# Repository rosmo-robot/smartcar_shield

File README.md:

# Smartcar shield 2.0

A versatile and easy to use vehicle platform for hobby & Academic projects

## Description
This repository, includes everything necessary to set up a Smartcar 2.0. The 100% open hardware robot down to component level.

The Smartcar, is a vehicular educational platform, which enables the user to develop various robotic applications in an affordable, pedagogic and easy way. It is intended to be accessible for persons with basic programming knowledge and little to no experience of electronics. It additionally supports the needs of more experienced users.

## Smartcar 2.0 (In development)

Licence: CERN-OHL-P

 Features;
 
 * Mounting space for SBC; Beagle AI64, Play, Pi, Jetson Nano, etc 
 * Reference implimentation of Arduino / [Smartcar Library](https://github.com/rosmo-robot/smartcar_shield/blob/master/README.md
 * Reference implimentation of [ROS2/Linorobot2](https://github.com/hippo5329/linorobot2_hardware)
 * Use of 4s LifePO4 or 3s Lipo batteries
 * Dual motor drivers for 4x4 & optional [mecanum drive](https://community.robotshop.com/forum/t/nema-17-mecanum-wheels/55901)
 * [mikroBUS socket](https://www.mikroe.com/mikrobus-shuttle-127mm-2x8-pin-box-header-smd-male)
 * Expanded I2C/ SPI connectors using [Breakout Garden](https://shop.pimoroni.com/collections/breakout-garden), [Qwiic](https://soldered.com/categories/easyc-2/)

### Project Status

 * [Motor board](https://kicanvas.org/?github=https://github.com/rosmo-robot/smartcar_shield/blob/master/extras/kicad/V2/Power/Power.kicad_pcb) ordered awaiting testing
   
 * [Pico board](https://kicanvas.org/?github=https://github.com/rosmo-robot/smartcar_shield/blob/master/extras/kicad/V2/Control/Pico/smartcar_control_2.0.kicad_pcb) ordered awaiting testing

We hope Smartcar 2.0 interesting to makers, schools and universities. We realise there's no such thing as a universal robot platform, and there are risks in trying to be all things to all people. We however drawn to seeing what's possible with modularity and testing the edges of interoperability.

### Smartcar 2.0 BOM (In development)

* 1 x [Motor board](https://kicanvas.org/?github=https://github.com/rosmo-robot/smartcar_shield/blob/master/extras/kicad/V2/Power/Power.kicad_pcb) ordered awaiting testing £11
* 1 X [Pico board](https://kicanvas.org/?github=https://github.com/rosmo-robot/smartcar_shield/blob/master/extras/kicad/V2/Control/Pico/smartcar_control_2.0.kicad_pcb) £5
* 4 x [Brushed motors](https://www.aliexpress.com/item/1005004242997257.html) (530rpm @ 12V) £40.50
* 1 x [Olimex Pico](https://www.olimex.com/Products/MicroPython/RP2040-PICO30/open-source-hardware)
* 2 x [40pin 2.54 pitch long male pin headers]()
* 1 x 3S [LifePO4 -recommended](https://www.pulsebattery.com/pages/search-results-page?q=lifePO4%203s) 105 x 33 x 25 or potentially dangerous 3S Lipo battery 135mm*42mm*25mm 304g [~$21 2200Mah](https://www.aliexpress.com/item/1005001419560964.html) > [~$38 4000Mah](https://www.aliexpress.com/item/1005004335619259.html) 135x42x21
* 2 x [Front Bumper](https://www.aliexpress.com/item/1005005024927428.html)

### Optional add ons

* - x [VL45L0x ToF distance sensors](https://shop.pimoroni.com/collections/breakout-garden?tags=Robotics) (optional)
* - X [BNO-85 IMU](https://learn.adafruit.com/adafruit-9-dof-orientation-imu-fusion-breakout-bno085?view=all) (Optional)
* - X [Servo controller](https://www.tindie.com/products/alexchu/zio-16-servo-controller-qwiic/)
* - X [line follower board](https://www.smart-prototyping.com/Zio-Line-Finder-Qwiic-4-Transceivers)
* - X [SPI or I2C Click boards](https://www.mikroe.com/click?interface*=spi,i2c,spi,i2c)
* - X [Aluminum base plate](https://www.aliexpress.com/i/4000265488897.html)
* - Whatever you can bolt to your compute module and get ROS2 to understand, eg cameras, Lidar

### Optional alternative Microcontroller Esp32 S3 (Waveshare)
- Used with [Smartcar Library](https://github.com/platisd/smartcar_shield#software)
- [Linorobot 2 via wifi transport](https://github.com/hippo5329/linorobot2_hardware)
- May also support [Microblocks](https://microblocks.fun/) 

### Single Board Computers (SBC)

We intend to develop some scripts for setting up robotics software on commonly used Single Board Computers which can be added to the basic microcontroller based platform. The OS will be Ubuntu 22.04 LTS. 

The supported hardware may include; 
- [Yuzuki chameleon (OSHW)](https://github.com/YuzukiHD/YuzukiChameleon)
- [Beaglebone Play](https://www.beagleboard.org/boards/beagleplay)
- [Beaglebone Ai-64 (OSHW)](https://beagleboard.org/ai-64) 

Installed software may include

 - Block editor code (TBC)
 - [Pyrobots](https://www.csc.liv.ac.uk/~lad/pyrobots/exercises.html) configuration script
 - [Python app providing a Webui for teleop](https://github.com/DIT112-V19/group-03) Pi GPIO > Micromod.  
 - [Python Robotics](https://github.com/AtsushiSakai/PythonRobotics) Pi GPIO > Micromod
 - [ROS2/Linorobot2](https://github.com/linorobot/linorobot2#linorobot2) USB > Micromod
 - [Rosboard](https://github.com/dheera/rosboard#rosboard) USB > Micromod
 - [Visual circuit](https://github.com/JdeRobot/VisualCircuit#visual-circuit) USB > Micromod
  - [LGPIO](https://ubuntu.com/tutorials/gpio-on-raspberry-pi#1-overview) & [script to set up GPIO](http://4tronix.co.uk/pi2go2/ipd03.py)
 - [Wetty](https://github.com/butlerx/wetty) with [Kaa](http://kaaedit.github.io/)
 - Some demo computer vision code

Linorobot:

### BLDC Version
- Offering an alternate/upgraded BLDC motor board using SimpleFOC, but re-using the 'Modules' board
- Perhaps using [Nema17 BLDC](https://www.omc-stepperonline.com/brushless-dc-motor?mfp=184-frame-size-mm[Nema%2017%20(42%20x%2042)]) to give access to [brackets](https://www.omc-stepperonline.com/nema-17-bracket-for-stepper-motor-and-geared-stepper-motor-alloy-steel-bracket-st-m1) & [gearboxes](https://www.aliexpress.com/premium/nema-17-gearbox.html)

### License
MIT & CERN-OHL-P for Smartcar 2.0 hardware

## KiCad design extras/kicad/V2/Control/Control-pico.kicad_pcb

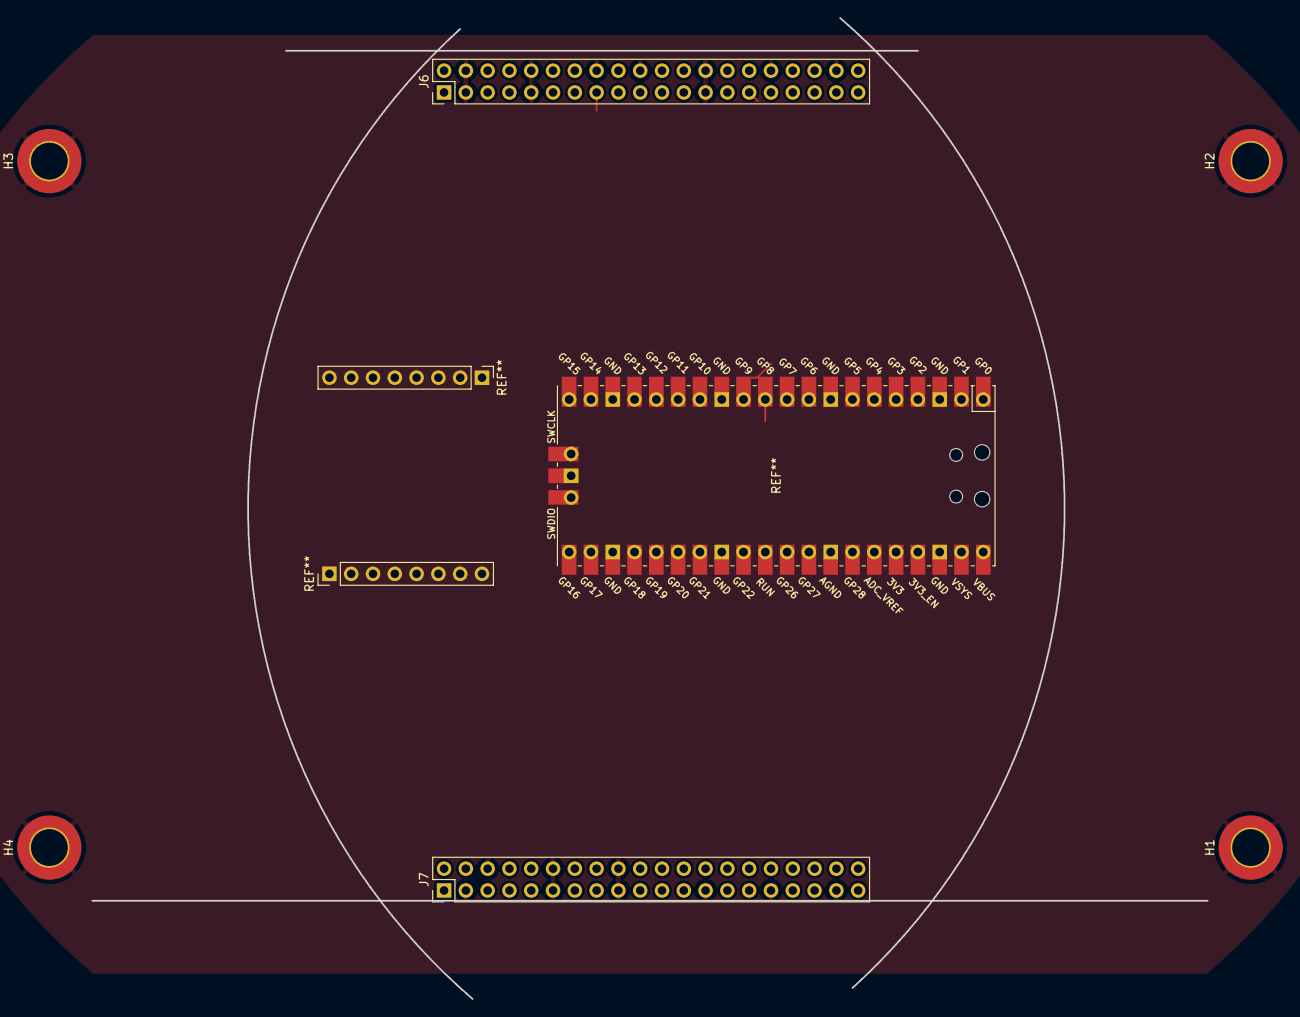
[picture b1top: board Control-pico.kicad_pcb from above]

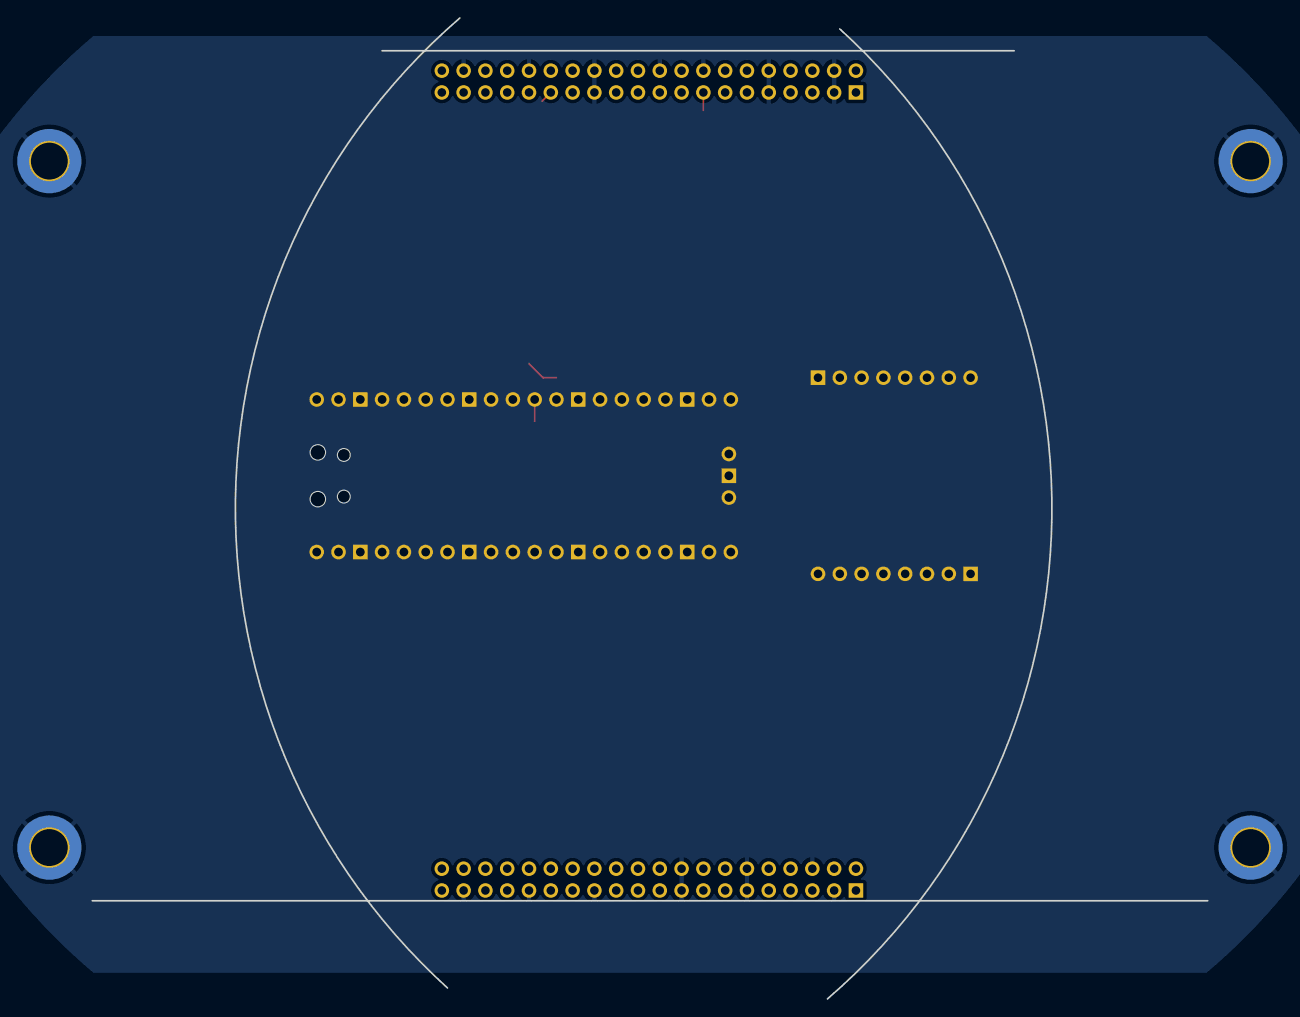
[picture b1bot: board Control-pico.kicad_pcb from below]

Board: 2 copper layers, 130.0 x 114.3 mm, 8 parts (2 on the bottom side), 3 nets.

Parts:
H1, H2, H3, H4: Hole; MountingHole_4.3mm_M4_DIN965_Pad_TopBottom
J6: left; PinHeader_2x20_P2.54mm_Vertical
J7: right; PinHeader_2x20_P2.54mm_Vertical
MH1, MH2: MountingHole_3.2mm_M3_DIN965

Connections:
+3V3: J6.5, J6.6, J6.7, J6.8, J6.19, J6.31, J7.30, J7.38
+5V: J7.13, J7.14, J7.15, J7.16
GND: H1.1, H2.1, H3.1, H4.1, J6.3, J6.4, J6.9, J6.10, J6.16, J6.20, J6.21, J6.25, J6.26, J6.32, J6.33, J6.38, J7.3, J7.6, J7.11, J7.12, J7.17, J7.18, J7.25, J7.31, J7.32, J7.37, J7.40

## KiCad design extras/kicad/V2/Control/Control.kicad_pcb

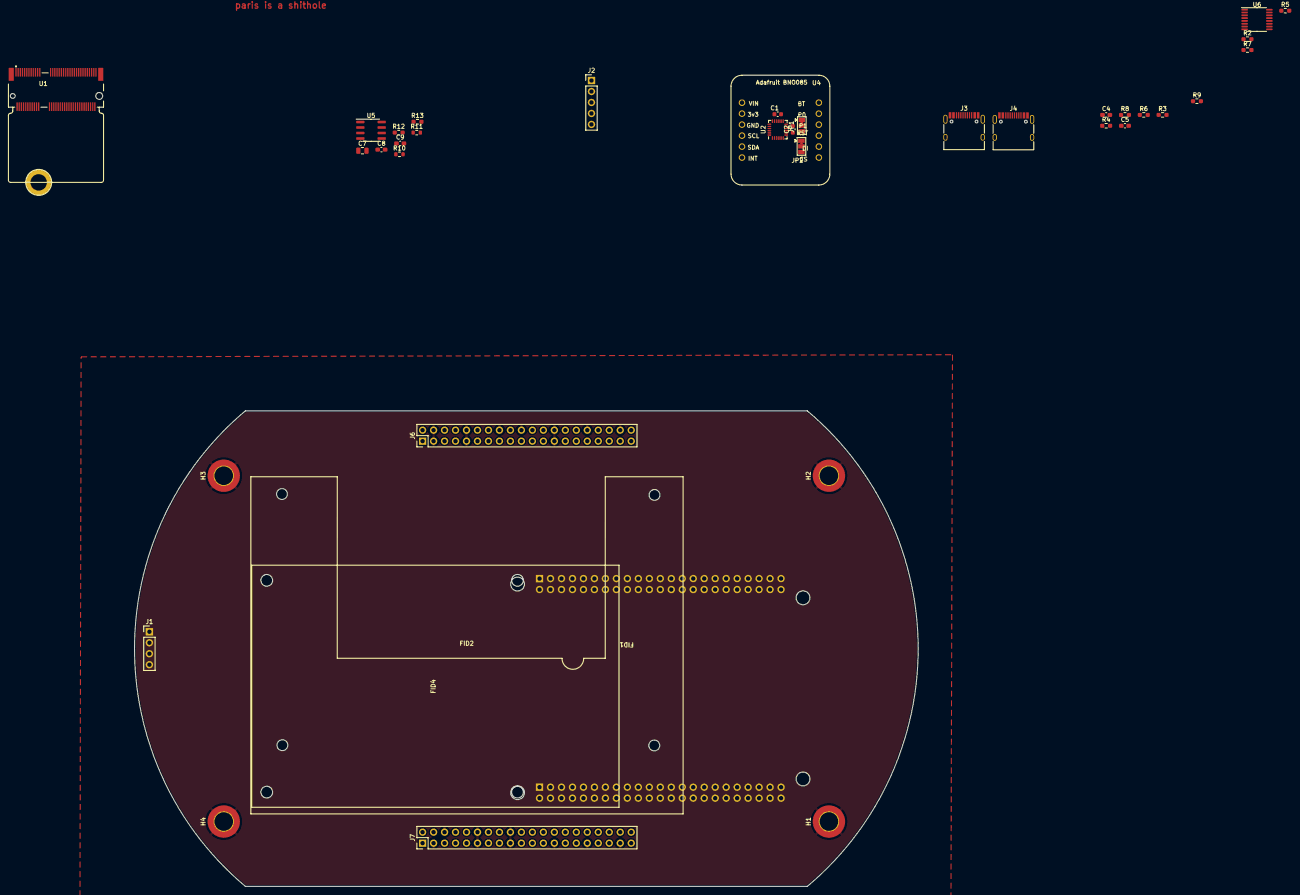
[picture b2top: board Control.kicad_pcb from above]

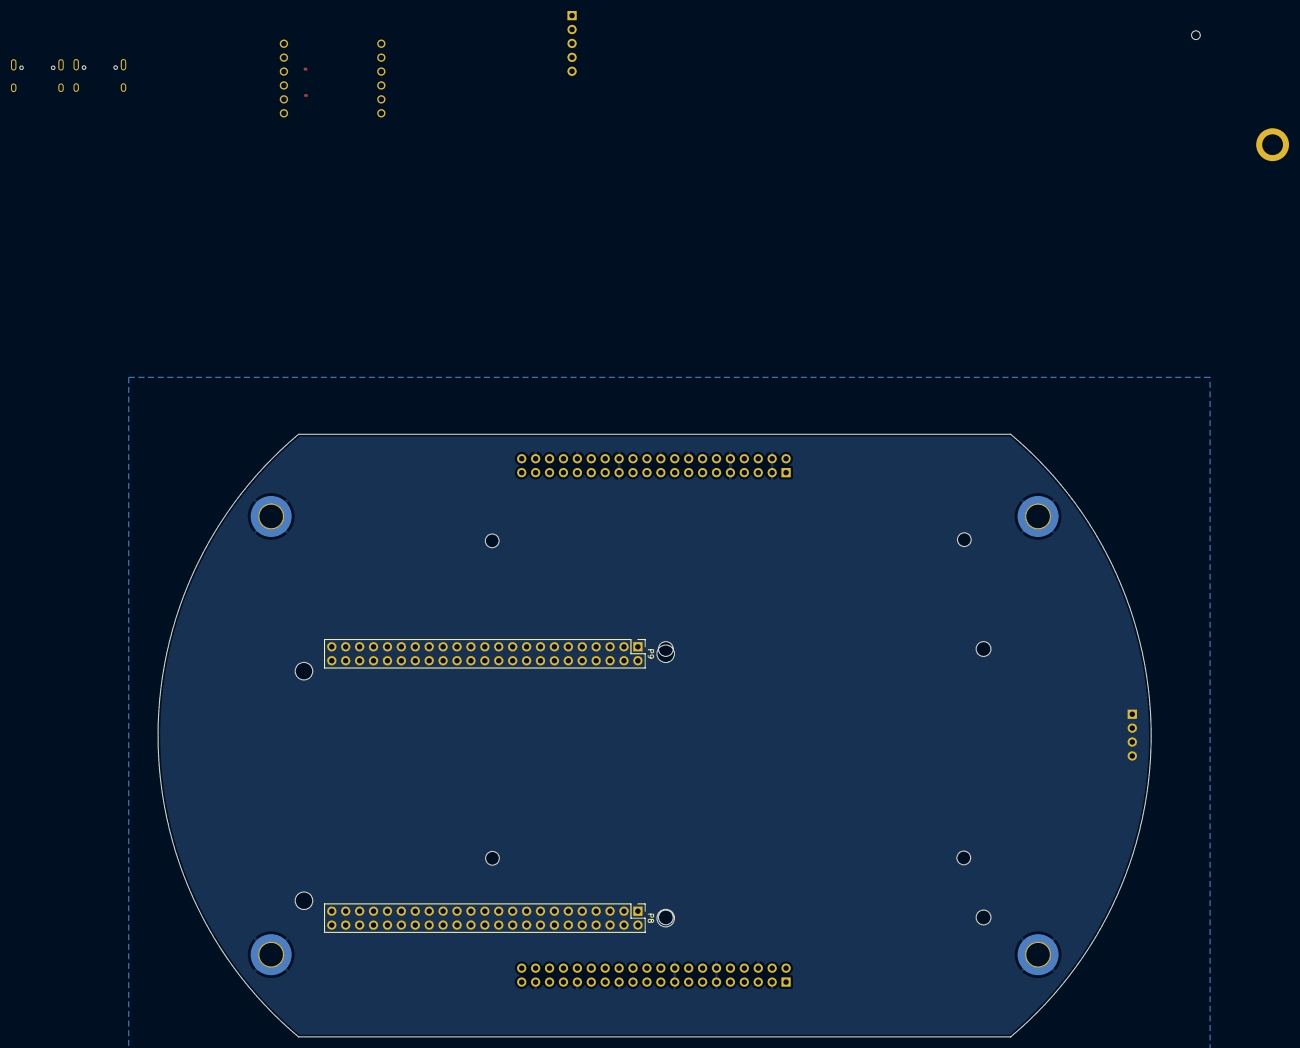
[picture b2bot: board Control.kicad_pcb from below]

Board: 2 copper layers, 181.3 x 110.0 mm, 45 parts (6 on the bottom side), 45 nets, no tracks yet.

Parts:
C1, C2: 100n; C_0603_1608Metric
C4, C8, C9: 100n; C_0603_1608Metric_Pad1.08x0.95mm_HandSolder
C5: 15p; C_0603_1608Metric_Pad1.08x0.95mm_HandSolder
C7: 22u; C_0805_2012Metric
FID1: Fiducial; AI-64
FID2: Fiducial; Jetson-NANO-mechanical
FID4: Fiducial; RPI4B-mechanical
H1, H2, H3, H4: Hole; MountingHole_4.3mm_M4_DIN965_Pad_TopBottom
J1: Ultrasonic Ranging; PinHeader_1x04_P2.54mm_Vertical
J2: Conn_01x05; PinHeader_1x05_P2.54mm_Vertical
J3: Output; USB_C_Receptacle_HRO_TYPE-C-31-M-12
J4: Input; USB_C_Receptacle_HRO_TYPE-C-31-M-12
J6: left; PinHeader_2x20_P2.54mm_Vertical
J7: right; PinHeader_2x20_P2.54mm_Vertical
JP1, JP2: set; SolderJumper-3_P1.3mm_Bridged12_Pad1.0x1.5mm
MH1, MH2, MH3, MH4: MountingHole_3.2mm_M3_DIN965
P8, P9: BeagleBone_Black_Header; PinHeader_2x23_P2.54mm_Vertical
R2: 2k7; R_0603_1608Metric_Pad0.98x0.95mm_HandSolder
R3, R4, R5, R6: 5k1; R_0603_1608Metric_Pad0.98x0.95mm_HandSolder
R7, R8: 1k; R_0603_1608Metric_Pad0.98x0.95mm_HandSolder
R9: 1Meg; R_0603_1608Metric_Pad0.98x0.95mm_HandSolder
R10, R11: 10k; R_0603_1608Metric
R12, R13: 120; R_0603_1608Metric_Pad0.98x0.95mm_HandSolder
U1: SparkFun-micromod; SparkFun-micromod-footprint
U2: MPU-6050; InvenSense_QFN-24_4x4mm_P0.5mm
U4: BNO085-breackout
U5: TJA1042T-3; SOIC-8_3.9x4.9mm_P1.27mm
U6: PCA9557PW; TSSOP-16_4.4x5mm_P0.65mm

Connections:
+3V3: C1.1, C2.1, C4.1, C9.1, J1.4, J2.5, J6.5, J6.6, J6.7, J6.8, J6.19, J6.31, J7.30, J7.38, JP1.3 (B), JP2.3 (B), P9.3, P9.4, R2.1, R7.1, R8.2, R10.1, R11.1, U1.2 (3v3), U1.74 (3V3), U2.8 (VDDIO), U2.13 (VDD), U4.1 (VIN), U5.5 (VIO), U6.16 (VDD)
+5V: C7.1, C8.1, J7.13, J7.14, J7.15, J7.16, P9.5, P9.6, U5.3 (VCC)
/CAN_H: R12.1, R13.1, U5.7 (CANH)
/CAN_L: R12.2, R13.2, U5.6 (CANL)
/Green_1: J6.29, U1.56 (AUD_OUT)
/Green_2: J6.17, U1.51 (I2C_SDA1)
/Green_3: J7.36, U1.52 (AUD_LRCLK)
/Green_4: J7.28, U1.17 (UART_TX1)
/INT_1: J2.2, U1.16 (I2C_INT), U2.12 (INT), U4.6 (INT)
/cc1: J3.A5 (CC1), J4.A5 (CC1), R3.1, R4.1
/cc2: J3.B5 (CC2), J4.B5 (CC2), R5.1, R6.1
/yellow_1: J6.27, U1.54 (AUD_IN)
/yellow_2: J6.15, U1.53 (I2C_SCL1)
/yellow_3: J7.34, U1.50 (AUD_BCLK)
/yellow_4: J7.26, U1.19 (UART_RX1)
AIN1_1: J6.39, U1.40 (G0/BUS0)
AIN1_2: J7.8, U1.48 (G4/BUS4)
AIN2_1: J6.37, U1.42 (G1/BUS1)
AIN2_2: J7.9, U1.44 (G2/BUS2)
BIN1_1: J6.34, U1.34 (A0)
BIN1_2: J7.5, U1.46 (G3/BUS3)
BIN2_1: J6.36, U1.38 (A1)
BIN2_2: J7.4, U1.73 (G5/BUS5)
D2+: J4.A6 (D+), J4.B6 (D+), U1.3 (USB_D+)
D2-: J4.A7 (D-), J4.B7 (D-), U1.5 (USB_D-)
D+: J3.A6 (D+), J3.B6 (D+)
D-: J3.A7 (D-), J3.B7 (D-)
GND: C1.2, C2.2, C4.2, C5.2, C7.2, C8.2, C9.2, H1.1, H2.1, H3.1, H4.1, J1.1, J2.1, J3.A1 (GND), J3.A12 (GND), J3.B1 (GND), J3.B12 (GND), J4.A1 (GND), J4.A12 (GND), J4.B1 (GND), J4.B12 (GND), J6.3, J6.4, J6.9, J6.10, J6.16, J6.20, J6.21, J6.25, J6.26, J6.32, J6.33, J6.38, J7.3, J7.6, J7.11, J7.12, J7.17, J7.18, J7.25, J7.31, J7.32, J7.37, J7.40, JP1.1 (A), JP2.1 (A), P8.1, P8.2, P8.45, P9.1, P9.2, P9.34, P9.43, P9.44, P9.45, P9.46, R3.2, R4.2, R5.2, R6.2, R9.1, U1.1 (GND), U1.7 (GND), U1.33 (GND), U1.36 (GND), U1.39 (GND), U1.45 (GND), U1.75 (GND), U2.18 (GND), U4.3 (GND), U5.2 (GND), U6.5 (A2), U6.8 (VSS)
unnamed: C5.1, J3.S1 (SHIELD), R9.2
unnamed: JP1.2 (C), U2.9 (AD0)
unnamed: JP2.2 (C), U4.8 (DI)
unnamed: R2.2, U6.15 (~RESET)
unnamed: R7.2, U6.3 (A0)
unnamed: R8.1, U6.4 (A1)
PWMA_1: J6.35, U1.10 (D0)
PWMA_2: J7.10, U1.18 (D1)
PWMB_1: J6.40, U1.32 (PWM0)
PWMB_2: J7.2, U1.47 (PWM1)
SCL: J1.3, J2.3, J6.1, P9.19, R10.2, U1.14 (I2C_SCL), U2.23 (SCL), U4.4 (SCL), U6.1 (SCL)
SDA: J1.2, J2.4, J6.2, P9.20, R11.2, U1.12 (I2C_SDA), U2.24 (SDA), U4.5 (SDA), U6.2 (SDA)
SPI_CS: P9.17, U1.55 (SPI_CS)
SPI_MISO: P9.29, U1.59 (SPI_COPI_(MOSI))
SPI_MOSI: P9.30, U1.61 (SPI_CIPO_(MISO))
SPI_SCK: P9.31, U1.57 (SPI_SCK)
VBUS: J3.A4 (VBUS), J3.A9 (VBUS), J3.B4 (VBUS), J3.B9 (VBUS), J4.A4 (VBUS), J4.A9 (VBUS), J4.B4 (VBUS), J4.B9 (VBUS), P9.7, P9.8

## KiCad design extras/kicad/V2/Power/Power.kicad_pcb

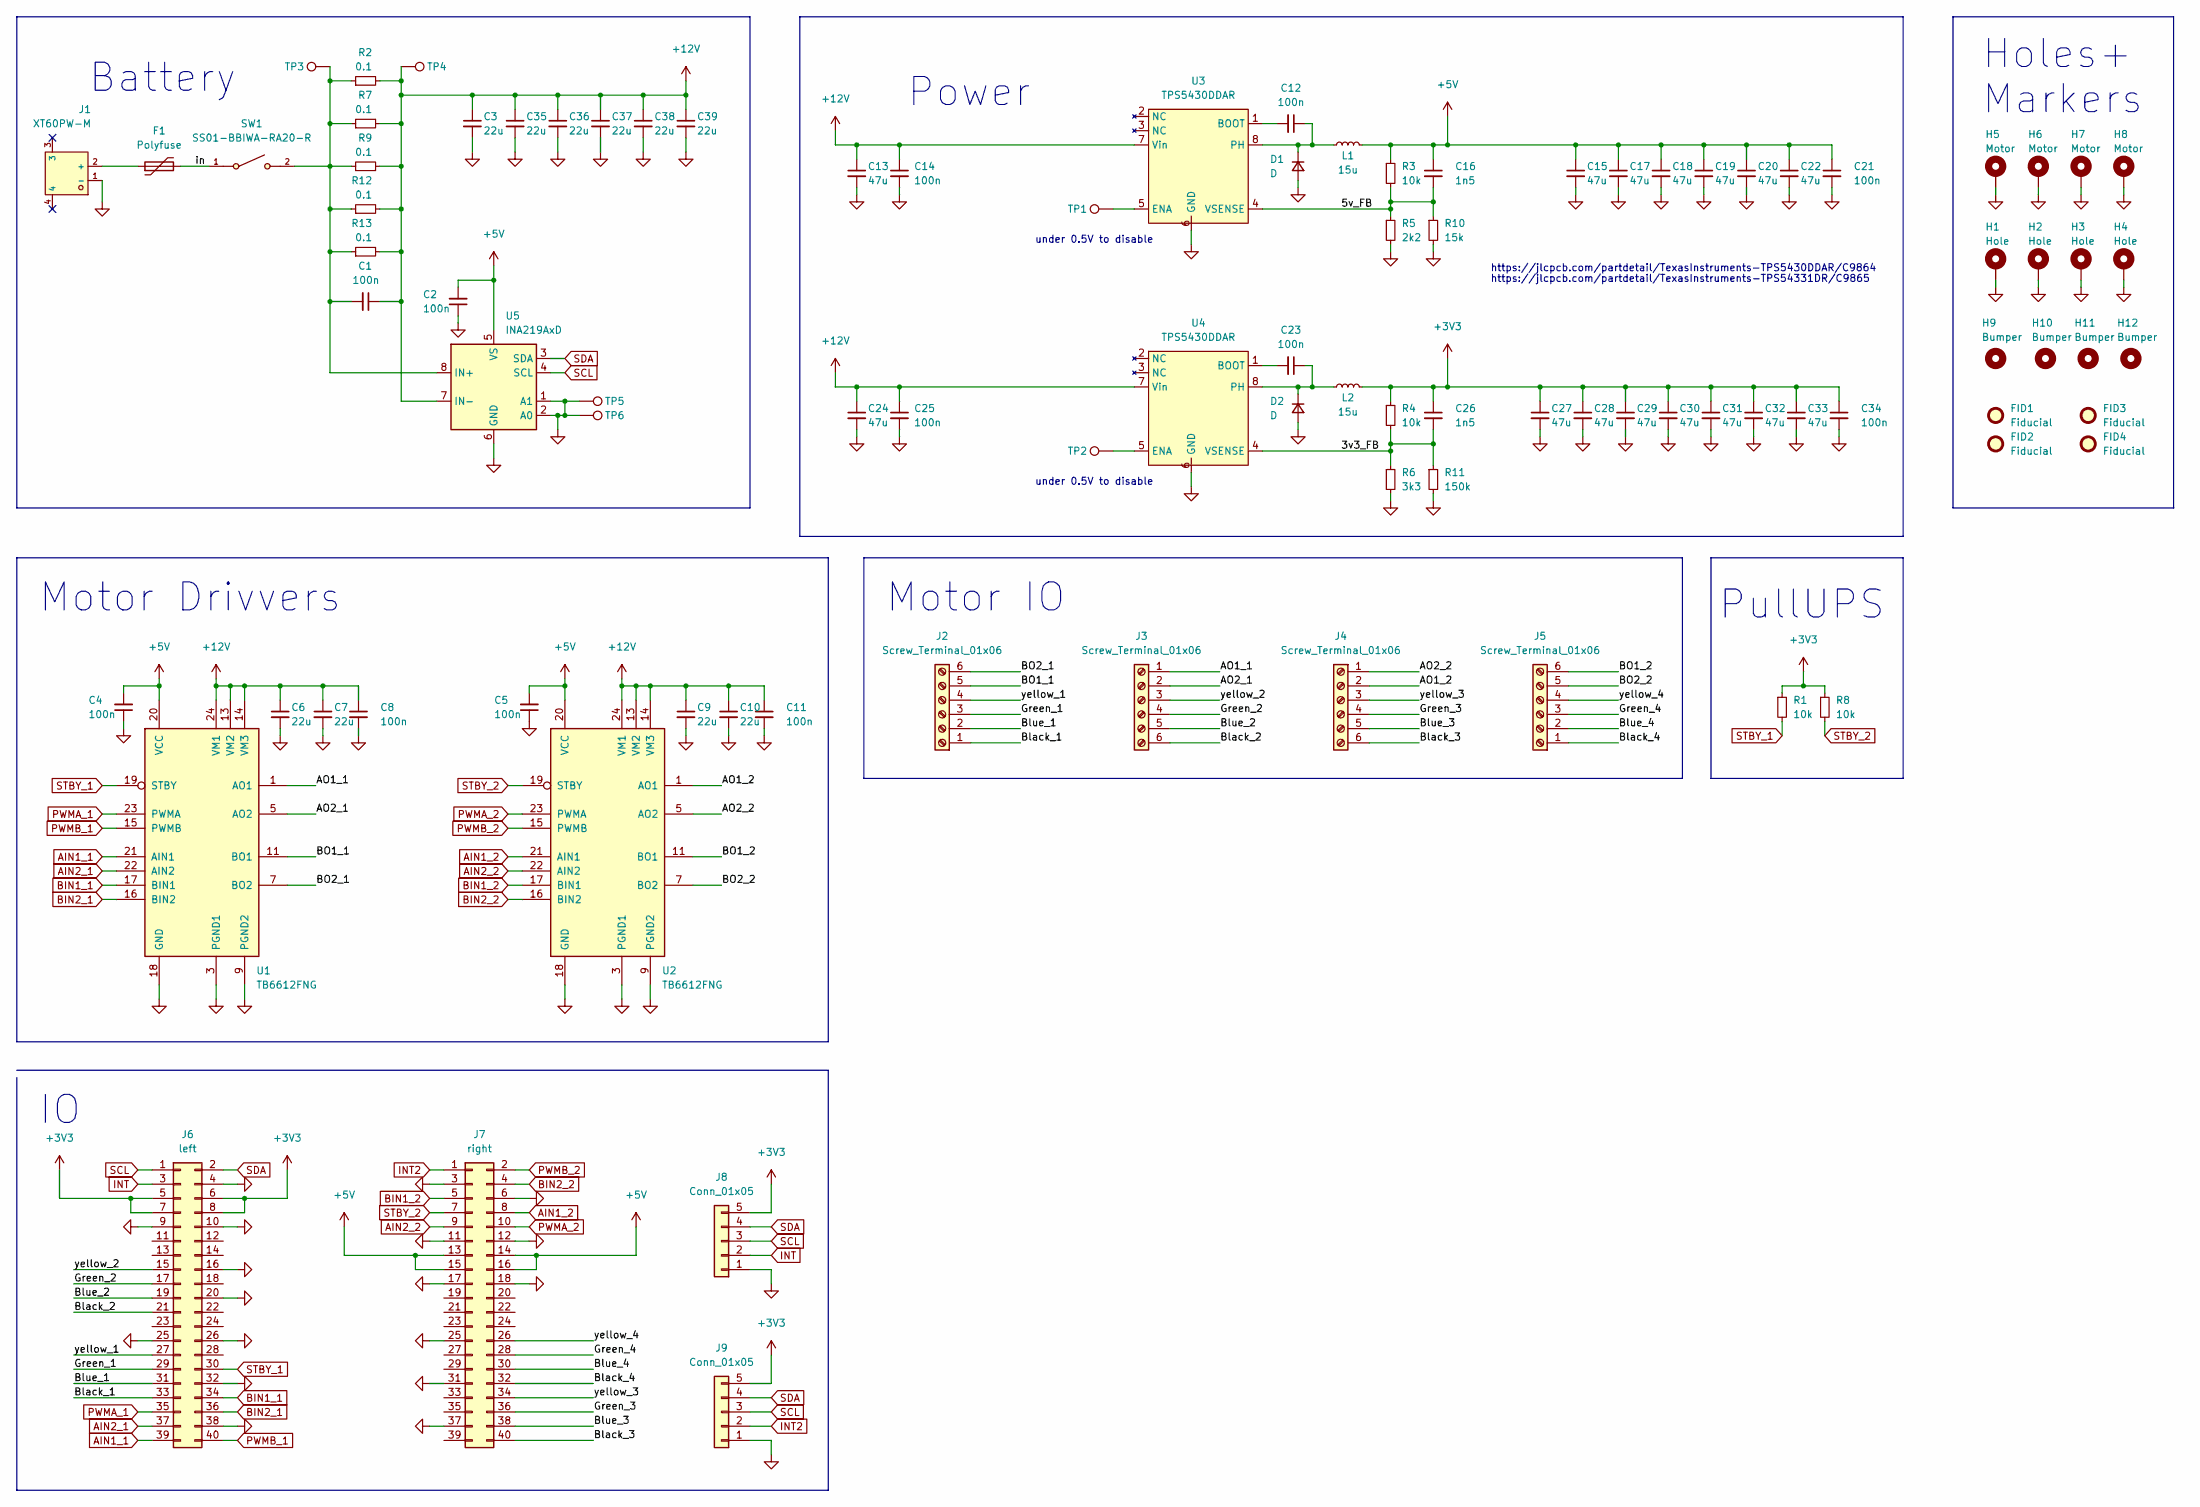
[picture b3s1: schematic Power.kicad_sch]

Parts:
C1, C2, C4, C5, C8, C11, C12, C14, C21, C23, C25, C34: 100n; C_0603_1608Metric; LCSC C14663
C3, C6, C7, C9, C10, C35, C36, C37, C38, C39: 22u; C_0805_2012Metric; LCSC C45783
C13, C15, C17, C18, C19, C20, C22, C24, C27, C28, C29, C30, C31, C32, C33: 47u; C_1206_3216Metric; LCSC C96123
C16, C26: 1n5; C_0603_1608Metric_Pad1.08x0.95mm_HandSolder; LCSC C1595
D1, D2: D; D_SMA; LCSC C22452
F1: Polyfuse; Fuse_2920_7451Metric_Pad2.10x5.45mm_HandSolder
FID1: Fiducial; Fiducial_0.5mm_Mask1mm
FID2: Fiducial; WEEE-Logo_5.6x8mm_SilkScreen
FID3: Fiducial; OSHW-Logo2_14.6x12mm_SilkScreen
FID4: Fiducial; KiCad-Logo2_6mm_SilkScreen
H1, H2, H3, H4: Hole; MountingHole_4.3mm_M4_DIN965_Pad_TopBottom
H5, H6, H7, H8: Motor; JGA25-370 DC motor
H9, H10, H11, H12: Bumper; MountingHole_4.5mm
J1: XT60PW-M; CONN-TH_XT60PW-M; LCSC C98732
J2, J3, J4, J5: Screw_Terminal_01x06; TerminalBlock_4Ucon_1x06_P3.50mm_Horizontal
J6: left; PinHeader_2x20_P2.54mm_Vertical
J7: right; PinHeader_2x20_P2.54mm_Vertical
J8, J9: Conn_01x05; PinHeader_1x05_P2.54mm_Vertical
L1, L2: 15u; Inductor SMD,11.6x10.1x4mm; LCSC C3002687
R1, R3, R4, R8: 10k; R_0603_1608Metric; LCSC C25804
R2, R7, R9, R12, R13: 0.1; R_1206_3216Metric_Pad1.30x1.75mm_HandSolder; LCSC C25334
R5: 2k2; R_0603_1608Metric_Pad0.98x0.95mm_HandSolder; LCSC C4190
R6: 3k3; R_0603_1608Metric_Pad0.98x0.95mm_HandSolder; LCSC C22978
R10: 15k; R_0603_1608Metric_Pad0.98x0.95mm_HandSolder; LCSC C22809
R11: 150k; R_0603_1608Metric_Pad0.98x0.95mm_HandSolder; LCSC C22807
SW1: SS01-BBIWA-RA20-R; SW-TH_SS01-BBIWA-RA20-R; LCSC C309065
TP1, TP2, TP3, TP4, TP5, TP6: TestPoint; TestPoint_Pad_D1.0mm
U1, U2: TB6612FNG; SSOP-24_5.3x8.2mm_P0.65mm; LCSC C88224
U3, U4: TPS5430DDAR; SOIC-8-1EP_3.9x4.9mm_P1.27mm_EP2.29x3mm_ThermalVias; LCSC C9864
U5: INA219AxD; SOIC-8_3.9x4.9mm_P1.27mm; LCSC C138706

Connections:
+3V3: C26.1, C27.1, C28.1, C29.1, C30.1, C31.1, C32.1, C33.1, C34.1, J6.5, J6.6, J6.7, J6.8, J8.5, J9.5, L2.2, R1.1, R4.1, R8.1
+5V: C2.2, C4.2, C5.2, C15.1, C16.1, C17.1, C18.1, C19.1, C20.1, C21.1, C22.1, J7.13, J7.14, J7.15, J7.16, L1.2, R3.1, U1.20 (VCC), U2.20 (VCC), U5.5 (VS)
+12V: C1.1, C3.1, C6.1, C7.1, C8.1, C9.1, C10.1, C11.1, C13.1, C14.1, C24.1, C25.1, C35.1, C36.1, C37.1, C38.1, C39.1, R2.2, R7.2, R9.2, R12.2, R13.2, TP4.1, U1.13 (VM2), U1.14 (VM3), U1.24 (VM1), U2.13 (VM2), U2.14 (VM3), U2.24 (VM1), U3.7 (Vin), U4.7 (Vin), U5.7 (IN-)
/3v3_FB: C26.2, R4.2, R6.1, R11.1, U4.4 (VSENSE)
/5v_FB: C16.2, R3.2, R5.1, R10.1, U3.4 (VSENSE)
/AO1_1: J3.1, U1.1 (AO1), U1.2 (AO1)
/AO1_2: J4.2, U2.1 (AO1), U2.2 (AO1)
/AO2_1: J3.2, U1.5 (AO2), U1.6 (AO2)
/AO2_2: J4.1, U2.5 (AO2), U2.6 (AO2)
/BO1_1: J2.5, U1.11 (BO1), U1.12 (BO1)
/BO1_2: J5.6, U2.11 (BO1), U2.12 (BO1)
/BO2_1: J2.6, U1.7 (BO2), U1.8 (BO2)
/BO2_2: J5.5, U2.7 (BO2), U2.8 (BO2)
/Black_1: J2.1, J6.33
/Black_2: J3.6, J6.21
/Black_3: J4.6, J7.40
/Black_4: J5.1, J7.32
/Blue_1: J2.2, J6.31
/Blue_2: J3.5, J6.19
/Blue_3: J4.5, J7.38
/Blue_4: J5.2, J7.30
/Green_1: J2.3, J6.29
/Green_2: J3.4, J6.17
/Green_3: J4.4, J7.36
/Green_4: J5.3, J7.28
/in: F1.2, SW1.1
/yellow_1: J2.4, J6.27
/yellow_2: J3.3, J6.15
/yellow_3: J4.3, J7.34
/yellow_4: J5.4, J7.26
AIN1_1: J6.39, U1.21 (AIN1)
AIN1_2: J7.8, U2.21 (AIN1)
AIN2_1: J6.37, U1.22 (AIN2)
AIN2_2: J7.9, U2.22 (AIN2)
BIN1_1: J6.34, U1.17 (BIN1)
BIN1_2: J7.5, U2.17 (BIN1)
BIN2_1: J6.36, U1.16 (BIN2)
BIN2_2: J7.4, U2.16 (BIN2)
GND: C2.1, C3.2, C4.1, C5.1, C6.2, C7.2, C8.2, C9.2, C10.2, C11.2, C13.2, C14.2, C15.2, C17.2, C18.2, C19.2, C20.2, C21.2, C22.2, C24.2, C25.2, C27.2, C28.2, C29.2, C30.2, C31.2, C32.2, C33.2, C34.2, C35.2, C36.2, C37.2, C38.2, C39.2, D1.2 (A), D2.2 (A), H1.1, H2.1, H3.1, H4.1, H5.1, H6.1, H7.1, H8.1, J1.1 (-), J6.4, J6.9, J6.10, J6.16, J6.20, J6.25, J6.26, J6.32, J6.38, J7.3, J7.6, J7.11, J7.12, J7.17, J7.18, J7.25, J7.31, J7.37, J8.1, J9.1, R5.2, R6.2, R10.2, R11.2, TP5.1, TP6.1, U1.3 (PGND1), U1.4 (PGND1), U1.9 (PGND2), U1.10 (PGND2), U1.18 (GND), U2.3 (PGND1), U2.4 (PGND1), U2.9 (PGND2), U2.10 (PGND2), U2.18 (GND), U3.6 (GND), U3.9 (Thermal), U4.6 (GND), U4.9 (Thermal), U5.1 (A1), U5.2 (A0), U5.6 (GND)
INT: J6.3, J8.2
INT2: J7.1, J9.2
unnamed: C1.2, R2.1, R7.1, R9.1, R12.1, R13.1, SW1.2, TP3.1, U5.8 (IN+)
unnamed: C12.1, D1.1 (K), L1.1, U3.8 (PH)
unnamed: C12.2, U3.1 (BOOT)
unnamed: C23.1, D2.1 (K), L2.1, U4.8 (PH)
unnamed: C23.2, U4.1 (BOOT)
unnamed: F1.1, J1.2 (+)
unnamed: TP1.1, U3.5 (ENA)
unnamed: TP2.1, U4.5 (ENA)
PWMA_1: J6.35, U1.23 (PWMA)
PWMA_2: J7.10, U2.23 (PWMA)
PWMB_1: J6.40, U1.15 (PWMB)
PWMB_2: J7.2, U2.15 (PWMB)
SCL: J6.1, J8.3, J9.3, U5.4 (SCL)
SDA: J6.2, J8.4, J9.4, U5.3 (SDA)
STBY_1: J6.30, R1.2, U1.19 (STBY)
STBY_2: J7.7, R8.2, U2.19 (STBY)

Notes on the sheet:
Motor IO
https://jlcpcb.com/partdetail/TexasInstruments-TPS5430DDAR/C9864
Motor Drivvers
https://jlcpcb.com/partdetail/TexasInstruments-TPS54331DR/C9865
under 0.5V to disable
PullUPS
Holes+ Markers
Battery
Power

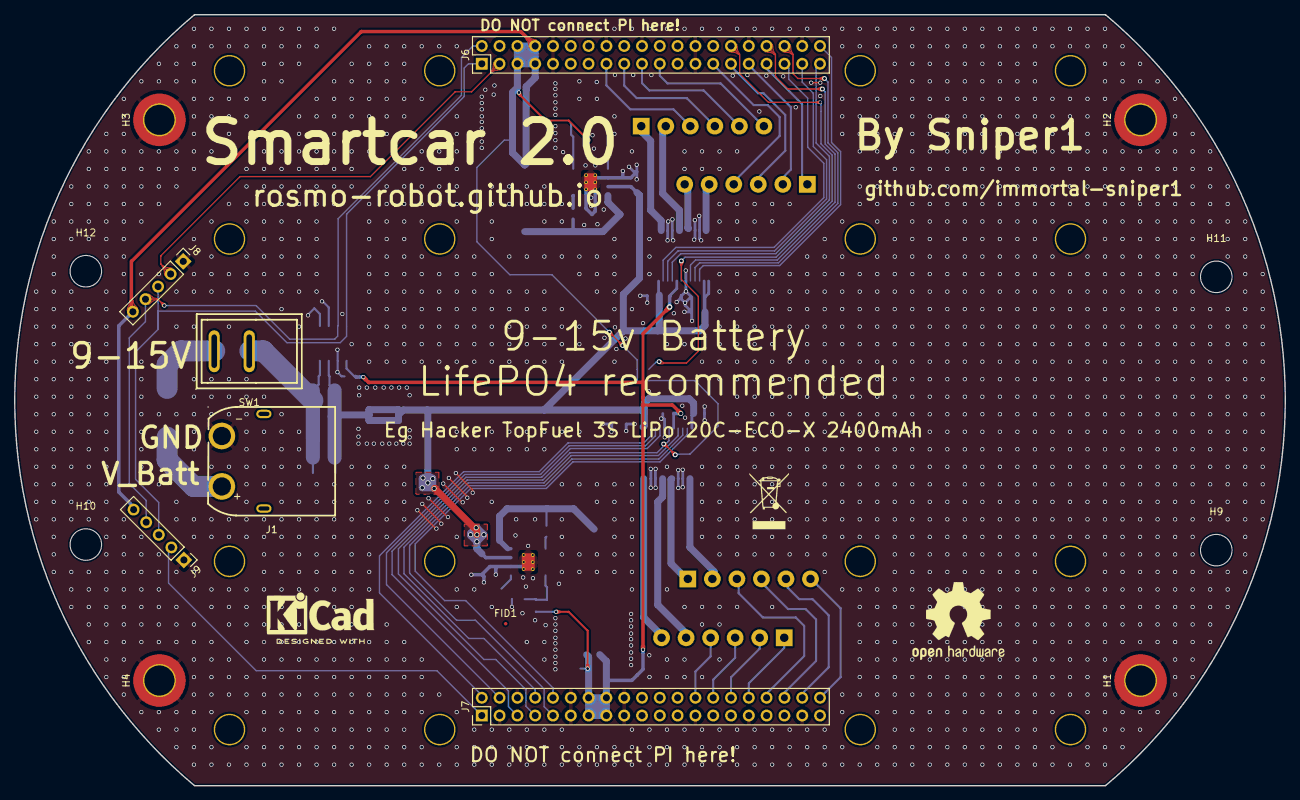
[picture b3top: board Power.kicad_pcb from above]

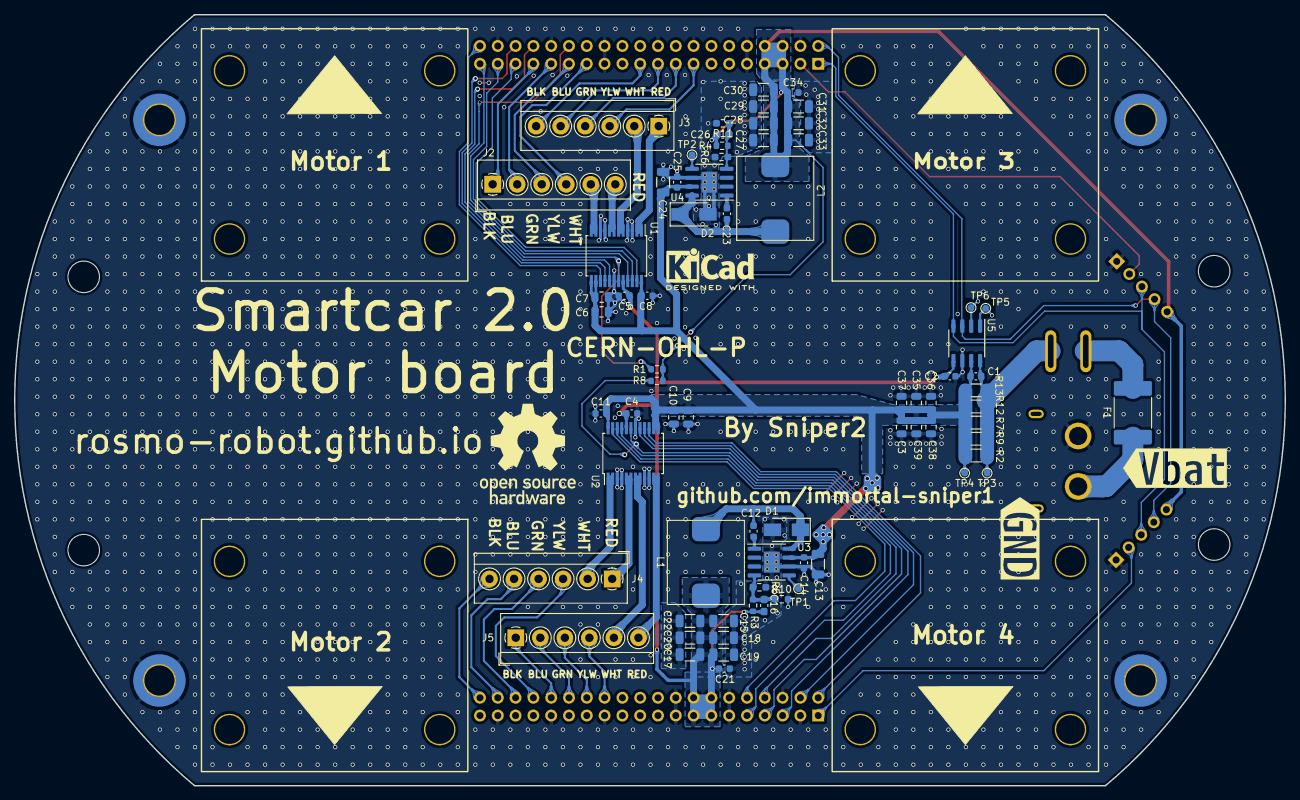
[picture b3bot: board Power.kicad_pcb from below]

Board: 2 copper layers, 181.3 x 110.0 mm, 96 parts (78 on the bottom side), 57 nets.

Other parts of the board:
kibuzzard-63E93541: G***; kibuzzard-63E93541
kibuzzard-63E93553: G***; kibuzzard-63E93553

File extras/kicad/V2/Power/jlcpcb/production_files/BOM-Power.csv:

Comment,Designator,Footprint,LCSC
INA219AxD,U5,SOIC-8_3.9x4.9mm_P1.27mm,C138706
100n,"C1,C11,C12,C14,C2,C21,C23,C25,C34,C4,C5,C8",C_0603_1608Metric,C14663
1n5,"C16,C26",C_0603_1608Metric_Pad1.08x0.95mm_HandSolder,C1595
D,"D1,D2",D_SMA,C22452
150k,R11,R_0603_1608Metric_Pad0.98x0.95mm_HandSolder,C22807
15k,R10,R_0603_1608Metric_Pad0.98x0.95mm_HandSolder,C22809
3k3,R6,R_0603_1608Metric_Pad0.98x0.95mm_HandSolder,C22978
0.1,"R12,R13,R2,R7,R9",R_1206_3216Metric_Pad1.30x1.75mm_HandSolder,C25334
10k,"R1,R3,R4,R8",R_0603_1608Metric,C25804
15u,"L1,L2","Inductor SMD,11.6x10.1x4mm",C3002687
SS01-BBIWA-RA20-R,SW1,SW-TH_SS01-BBIWA-RA20-R,C309065
2k2,R5,R_0603_1608Metric_Pad0.98x0.95mm_HandSolder,C4190
22u,"C10,C3,C35,C36,C37,C38,C39,C6,C7,C9",C_0805_2012Metric,C45783
TB6612FNG,"U1,U2",SSOP-24_5.3x8.2mm_P0.65mm,C88224
47u,"C13,C15,C17,C18,C19,C20,C22,C24,C27,C28,C29,C30,C31,C32,C33",C_1206_3216Metric,C96123
TPS5430DDAR,"U3,U4",SOIC-8-1EP_3.9x4.9mm_P1.27mm_EP2.29x3mm_ThermalVias,C9864
XT60PW-M,J1,CONN-TH_XT60PW-M,C98732
Conn_01x05,J8,PinHeader_1x05_P2.54mm_Vertical,
left,J6,PinHeader_2x20_P2.54mm_Vertical,
Conn_01x05,J9,PinHeader_1x05_P2.54mm_Vertical,
right,J7,PinHeader_2x20_P2.54mm_Vertical,
Polyfuse,F1,Fuse_2920_7451Metric_Pad2.10x5.45mm_HandSolder,
Screw_Terminal_01x06,J3,TerminalBlock_4Ucon_1x06_P3.50mm_Horizontal,
Screw_Terminal_01x06,J5,TerminalBlock_4Ucon_1x06_P3.50mm_Horizontal,
Screw_Terminal_01x06,J4,TerminalBlock_4Ucon_1x06_P3.50mm_Horizontal,
Screw_Terminal_01x06,J2,TerminalBlock_4Ucon_1x06_P3.50mm_Horizontal,

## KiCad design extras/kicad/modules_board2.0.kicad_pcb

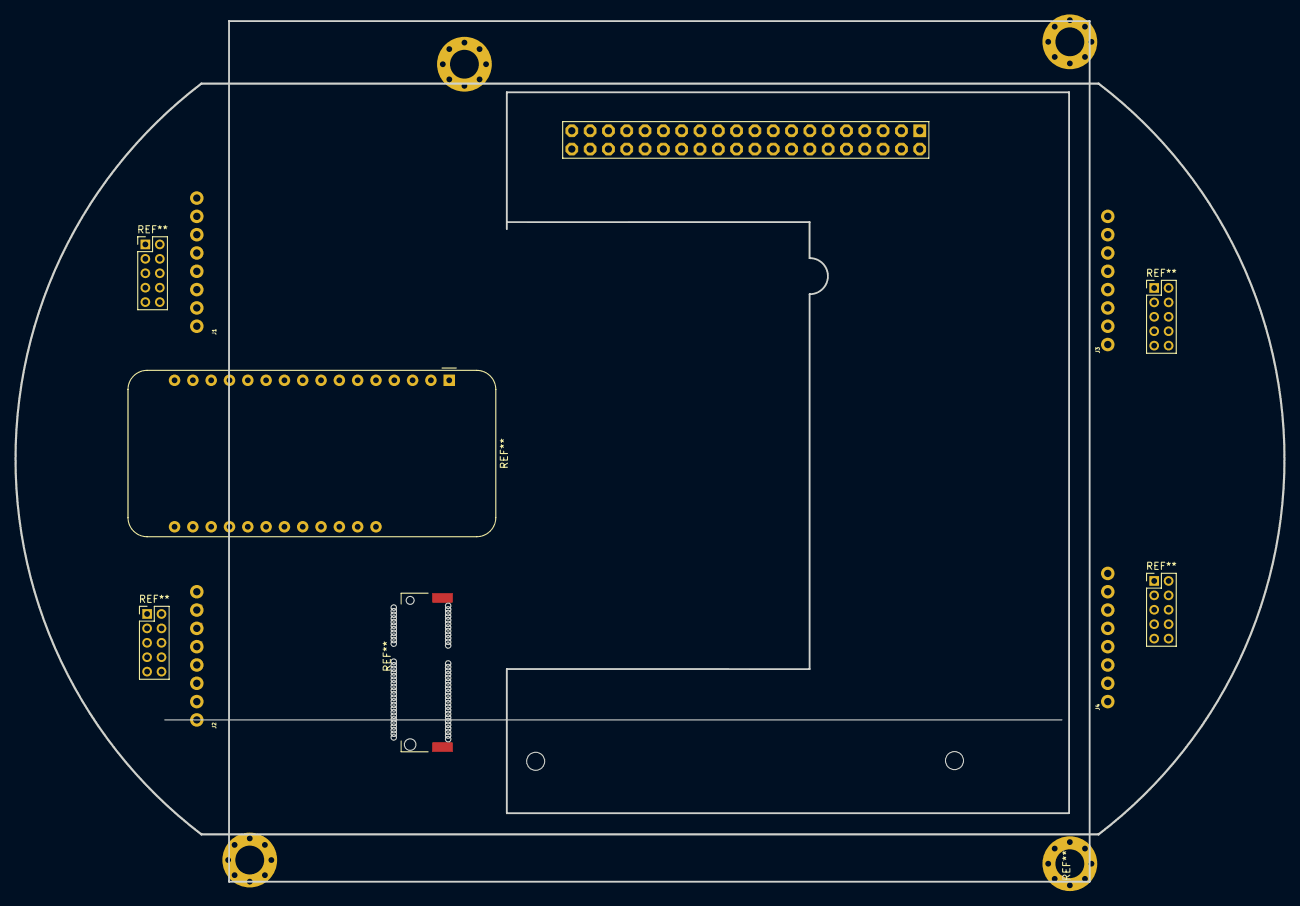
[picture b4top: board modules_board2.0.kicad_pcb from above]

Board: 2 copper layers, 176.0 x 119.4 mm, 4 parts (0 on the bottom side), 4 nets.

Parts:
J1, J2, J3, J4: 1X08_NO_SILK

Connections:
BAT_GND: J1.1, J3.1
GND: J2.8, J4.8
MOTOR_VCC: J2.3, J4.2
VCC: J2.2, J4.1
